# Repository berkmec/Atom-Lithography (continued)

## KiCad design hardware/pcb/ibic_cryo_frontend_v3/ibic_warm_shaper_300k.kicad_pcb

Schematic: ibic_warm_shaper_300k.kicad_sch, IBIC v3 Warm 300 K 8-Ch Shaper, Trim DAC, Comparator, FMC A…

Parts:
CAA0, CAA1, CAA2, CAA3, CAA4, CAA5, CAA6, CAA7: 120pF_C0G_1pct; C_0402_1005Metric; MPN 120pF_C0G_1pct
CD0BN, CD0BP, CD0C, CD0EN, CD0EP, CD1BN, CD1BP, CD1C, CD1EN, CD1EP, CD2BN, CD2BP, CD2C, CD2EN, CD2EP, CD3BN, CD3BP, CD3C, CD3EN, CD3EP, CD4BN, CD4BP, CD4C, CD4EN, CD4EP, CD5BN, CD5BP, CD5C, CD5EN, CD5EP, CD6BN, CD6BP, CD6C, CD6EN, CD6EP, CD7BN, CD7BP, CD7C, CD7EN, CD7EP: 100nF_C0G; C_0402_1005Metric; MPN 100nF_C0G
CDAC0, CDAC1, CDAC2, CDAC3, CDAC4, CDAC5, CDAC6, CDAC7: 100nF_C0G; C_0402_1005Metric; MPN 100nF_C0G
CD_DAC: 100nF_C0G; C_0402_1005Metric; MPN 100nF_C0G
CIN_ULDO_D3V3: 10uF_25V_X7R; C_0805_2012Metric; MPN 10uF_25V_X7R
CIN_ULDO_N2V5, CIN_ULDO_N5A: 10uF_25V_X7R; C_0805_2012Metric; MPN 10uF_25V_X7R
CIN_ULDO_P2V5, CIN_ULDO_P5A: 10uF_25V_X7R; C_0805_2012Metric; MPN 10uF_25V_X7R
COUT_ULDO_D3V3: 10uF_10V_X7R; C_0805_2012Metric; MPN 10uF_10V_X7R
COUT_ULDO_N2V5, COUT_ULDO_N5A: 10uF_10V_X7R; C_0805_2012Metric; MPN 10uF_10V_X7R
COUT_ULDO_P2V5, COUT_ULDO_P5A: 10uF_10V_X7R; C_0805_2012Metric; MPN 10uF_10V_X7R
CP0, CP1, CP2, CP3, CP4, CP5, CP6, CP7: 600pF_C0G_1pct; C_0603_1608Metric; MPN 600pF_C0G_1pct
CREF_DAC: 100nF_C0G; C_0402_1005Metric; MPN 100nF_C0G
CS0, CS1, CS2, CS3, CS4, CS5, CS6, CS7: 600pF_C0G_1pct; C_0603_1608Metric; MPN 600pF_C0G_1pct
CSET_ULDO_D3V3: 4.7uF_10V_X7R; C_0603_1608Metric; MPN 4.7uF_10V_X7R
CSET_ULDO_N2V5, CSET_ULDO_N5A: 4.7uF_10V_X7R; C_0603_1608Metric; MPN 4.7uF_10V_X7R
CSET_ULDO_P2V5, CSET_ULDO_P5A: 4.7uF_10V_X7R; C_0603_1608Metric; MPN 4.7uF_10V_X7R
JADC: FMC_PHA_ADC_TAP_16P; HDR_2x8_2.54mm; MPN FMC_PHA_ADC_TAP_16P
JFPGA: FPGA_COUNT_SPI_24P; HDR_2x12_2.54mm; MPN FPGA_COUNT_SPI_24P
JIN0, JIN1, JIN2, JIN3, JIN4, JIN5, JIN6, JIN7: SMA_50R_FROM_CF63; SMA_EdgeMount; MPN SMA_50R_FROM_CF63
JPWR_COLD_OUT: HDR_6P_CLEAN_REG_OUT; HDR_1x6_2.54mm; MPN HDR_6P_CLEAN_REG_OUT
JPWR_RAW: HDR_6P_LINEAR_PSU_IN; HDR_1x6_2.54mm; MPN HDR_6P_LINEAR_PSU_IN
RAA0, RAA1, RAA2, RAA3, RAA4, RAA5, RAA6, RAA7: 49.9R_1pct; R_0402_1005Metric; MPN 49.9R_1pct
RDAC0, RDAC1, RDAC2, RDAC3, RDAC4, RDAC5, RDAC6, RDAC7: 1.00k_1pct; R_0402_1005Metric; MPN 1.00k_1pct
RG10, RG11, RG12, RG13, RG14, RG15, RG16, RG17: 100R_0.1pct; R_0402_1005Metric; MPN 100R_0.1pct
RG20, RG21, RG22, RG23, RG24, RG25, RG26, RG27: 13.5k_0.1pct; R_0402_1005Metric; MPN 13.5k_0.1pct
RHYS10, RHYS11, RHYS12, RHYS13, RHYS14, RHYS15, RHYS16, RHYS17: 1.00k_1pct; R_0402_1005Metric; MPN 1.00k_1pct
RHYS20, RHYS21, RHYS22, RHYS23, RHYS24, RHYS25, RHYS26, RHYS27: 1.00M_1pct; R_0402_1005Metric; MPN 1.00M_1pct
RRX0, RRX1, RRX2, RRX3, RRX4, RRX5, RRX6, RRX7: 49.9R_1pct; R_0402_1005Metric; MPN 49.9R_1pct
RS10, RS11, RS12, RS13, RS14, RS15, RS16, RS17, RS20, RS21, RS22, RS23, RS24, RS25, RS26, RS27: 2.00k_0.1pct; R_0402_1005Metric; MPN 2.00k_0.1pct
RSET_ULDO_D3V3: 33.2k_0.1pct; R_0402_1005Metric; MPN 33.2k_0.1pct
RSET_ULDO_N2V5: 24.9k_0.1pct; R_0402_1005Metric; MPN 24.9k_0.1pct
RSET_ULDO_N5A: 49.9k_0.1pct; R_0402_1005Metric; MPN 49.9k_0.1pct
RSET_ULDO_P2V5: 24.9k_0.1pct; R_0402_1005Metric; MPN 24.9k_0.1pct
RSET_ULDO_P5A: 49.9k_0.1pct; R_0402_1005Metric; MPN 49.9k_0.1pct
RTERM0, RTERM1, RTERM2, RTERM3, RTERM4, RTERM5, RTERM6, RTERM7: 49.9R_1pct; R_0402_1005Metric; MPN 49.9R_1pct
R_STAR: 0R_STAR_GND; R_0603_1608Metric; MPN 0R_STAR_GND
U0B, U1B, U2B, U3B, U4B, U5B, U6B, U7B: ADA4817-1_SHAPER; SOIC-8-1EP_3.9x4.9mm_P1.27mm; MPN ADA4817-1ARDZ
U0C, U1C, U2C, U3C, U4C, U5C, U6C, U7C: TLV3501_CMP_4p5NS; SOT-23-6; MPN TLV3501AIDBVR
U0E, U1E, U2E, U3E, U4E, U5E, U6E, U7E: ADA4817-1_ADC_BUF; SOIC-8-1EP_3.9x4.9mm_P1.27mm; MPN ADA4817-1ARDZ
UDAC: DAC8568_16B_8CH_SPI; TSSOP-16_4.4x5mm_P0.65mm; MPN DAC8568ICPWR
ULDO_D3V3: LT3045_D3V3_LDO; MSOP-12-1EP_3x4mm_P0.65mm; MPN LT3045EMSE
ULDO_N2V5: LT3094_N2V5_LDO; MSOP-12-1EP_3x4mm_P0.65mm; MPN LT3094EMSE
ULDO_N5A: LT3094_N5V_LDO; MSOP-12-1EP_3x4mm_P0.65mm; MPN LT3094EMSE
ULDO_P2V5: LT3045_P2V5_LDO; MSOP-12-1EP_3x4mm_P0.65mm; MPN LT3045EMSE
ULDO_P5A: LT3045_P5V_LDO; MSOP-12-1EP_3x4mm_P0.65mm; MPN LT3045EMSE

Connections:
AGND: CAA0.2, CAA1.2, CAA2.2, CAA3.2, CAA4.2, CAA5.2, CAA6.2, CAA7.2, CD0BN.2, CD0BP.2, CD0EN.2, CD0EP.2, CD1BN.2, CD1BP.2, CD1EN.2, CD1EP.2, CD2BN.2, CD2BP.2, CD2EN.2, CD2EP.2, CD3BN.2, CD3BP.2, CD3EN.2, CD3EP.2, CD4BN.2, CD4BP.2, CD4EN.2, CD4EP.2, CD5BN.2, CD5BP.2, CD5EN.2, CD5EP.2, CD6BN.2, CD6BP.2, CD6EN.2, CD6EP.2, CD7BN.2, CD7BP.2, CD7EN.2, CD7EP.2, CDAC0.2, CDAC1.2, CDAC2.2, CDAC3.2, CDAC4.2, CDAC5.2, CDAC6.2, CDAC7.2, CIN_ULDO_N2V5.2, CIN_ULDO_N5A.2, CIN_ULDO_P2V5.2, CIN_ULDO_P5A.2, COUT_ULDO_N2V5.2, COUT_ULDO_N5A.2, COUT_ULDO_P2V5.2, COUT_ULDO_P5A.2, CP0.2, CP1.2, CP2.2, CP3.2, CP4.2, CP5.2, CP6.2, CP7.2, CREF_DAC.2, CSET_ULDO_N2V5.2, CSET_ULDO_N5A.2, CSET_ULDO_P2V5.2, CSET_ULDO_P5A.2, JADC.2, JADC.4, JADC.6, JADC.8, JADC.10, JADC.12, JADC.14, JADC.16, JIN0.2 (GND), JIN1.2 (GND), JIN2.2 (GND), JIN3.2 (GND), JIN4.2 (GND), JIN5.2 (GND), JIN6.2 (GND), JIN7.2 (GND), JPWR_COLD_OUT.5 (AGND1), JPWR_COLD_OUT.6 (AGND2), JPWR_RAW.5 (AGND1), JPWR_RAW.6 (AGND2), RG10.2, RG11.2, RG12.2, RG13.2, RG14.2, RG15.2, RG16.2, RG17.2, RRX0.2, RRX1.2, RRX2.2, RRX3.2, RRX4.2, RRX5.2, RRX6.2, RRX7.2, RS10.2, RS11.2, RS12.2, RS13.2, RS14.2, RS15.2, RS16.2, RS17.2, RSET_ULDO_N2V5.2, RSET_ULDO_N5A.2, RSET_ULDO_P2V5.2, RSET_ULDO_P5A.2, R_STAR.1, ULDO_N2V5.6 (ILIM), ULDO_N2V5.9 (GND), ULDO_N5A.6 (ILIM), ULDO_N5A.9 (GND), ULDO_P2V5.6 (ILIM), ULDO_P2V5.8 (GND), ULDO_P2V5.13 (EP_GND), ULDO_P5A.6 (ILIM), ULDO_P5A.8 (GND), ULDO_P5A.13 (EP_GND)
CH0.CMP_INP: RHYS10.2, RHYS20.1, U0C.3 (IN+)
CH0.CMP_OUT: RHYS20.2, RTERM0.1, U0C.5 (OUT)
CH0.COAX_IN: CS0.1, JIN0.1 (SIG), RRX0.1
CH0.COUNT_HIT: JFPGA.1, RTERM0.2
CH0.CR_OUT: CS0.2, RS10.1, U0B.3 (IN+)
CH0.SHP_ADC: CAA0.1, JADC.1, RAA0.2
CH0.SHP_BUF: RAA0.1, RHYS10.1, U0E.1 (FB), U0E.2 (IN-), U0E.6 (OUT)
CH0.SHP_FB: RG10.1, RG20.1, U0B.2 (IN-)
CH0.SHP_GAIN: RG20.2, RS20.1, U0B.1 (FB), U0B.6 (OUT)
CH0.SHP_OUT: CP0.1, RS20.2, U0E.3 (IN+)
CH0.THRESH: CDAC0.1, RDAC0.2, U0C.1 (IN-)
CH0.THRESH_RAW: RDAC0.1, UDAC.4
CH1.CMP_INP: RHYS11.2, RHYS21.1, U1C.3 (IN+)
CH1.CMP_OUT: RHYS21.2, RTERM1.1, U1C.5 (OUT)
CH1.COAX_IN: CS1.1, JIN1.1 (SIG), RRX1.1
CH1.COUNT_HIT: JFPGA.2, RTERM1.2
CH1.CR_OUT: CS1.2, RS11.1, U1B.3 (IN+)
CH1.SHP_ADC: CAA1.1, JADC.3, RAA1.2
CH1.SHP_BUF: RAA1.1, RHYS11.1, U1E.1 (FB), U1E.2 (IN-), U1E.6 (OUT)
CH1.SHP_FB: RG11.1, RG21.1, U1B.2 (IN-)
CH1.SHP_GAIN: RG21.2, RS21.1, U1B.1 (FB), U1B.6 (OUT)
CH1.SHP_OUT: CP1.1, RS21.2, U1E.3 (IN+)
CH1.THRESH: CDAC1.1, RDAC1.2, U1C.1 (IN-)
CH1.THRESH_RAW: RDAC1.1, UDAC.5
CH2.CMP_INP: RHYS12.2, RHYS22.1, U2C.3 (IN+)
CH2.CMP_OUT: RHYS22.2, RTERM2.1, U2C.5 (OUT)
CH2.COAX_IN: CS2.1, JIN2.1 (SIG), RRX2.1
CH2.COUNT_HIT: JFPGA.3, RTERM2.2
CH2.CR_OUT: CS2.2, RS12.1, U2B.3 (IN+)
CH2.SHP_ADC: CAA2.1, JADC.5, RAA2.2
CH2.SHP_BUF: RAA2.1, RHYS12.1, U2E.1 (FB), U2E.2 (IN-), U2E.6 (OUT)
CH2.SHP_FB: RG12.1, RG22.1, U2B.2 (IN-)
CH2.SHP_GAIN: RG22.2, RS22.1, U2B.1 (FB), U2B.6 (OUT)
CH2.SHP_OUT: CP2.1, RS22.2, U2E.3 (IN+)
CH2.THRESH: CDAC2.1, RDAC2.2, U2C.1 (IN-)
CH2.THRESH_RAW: RDAC2.1, UDAC.6
CH3.CMP_INP: RHYS13.2, RHYS23.1, U3C.3 (IN+)
CH3.CMP_OUT: RHYS23.2, RTERM3.1, U3C.5 (OUT)
CH3.COAX_IN: CS3.1, JIN3.1 (SIG), RRX3.1
CH3.COUNT_HIT: JFPGA.4, RTERM3.2
CH3.CR_OUT: CS3.2, RS13.1, U3B.3 (IN+)
CH3.SHP_ADC: CAA3.1, JADC.7, RAA3.2
CH3.SHP_BUF: RAA3.1, RHYS13.1, U3E.1 (FB), U3E.2 (IN-), U3E.6 (OUT)
CH3.SHP_FB: RG13.1, RG23.1, U3B.2 (IN-)
CH3.SHP_GAIN: RG23.2, RS23.1, U3B.1 (FB), U3B.6 (OUT)
CH3.SHP_OUT: CP3.1, RS23.2, U3E.3 (IN+)
CH3.THRESH: CDAC3.1, RDAC3.2, U3C.1 (IN-)
CH3.THRESH_RAW: RDAC3.1, UDAC.7
CH4.CMP_INP: RHYS14.2, RHYS24.1, U4C.3 (IN+)
CH4.CMP_OUT: RHYS24.2, RTERM4.1, U4C.5 (OUT)
CH4.COAX_IN: CS4.1, JIN4.1 (SIG), RRX4.1
CH4.COUNT_HIT: JFPGA.5, RTERM4.2
CH4.CR_OUT: CS4.2, RS14.1, U4B.3 (IN+)
CH4.SHP_ADC: CAA4.1, JADC.9, RAA4.2
CH4.SHP_BUF: RAA4.1, RHYS14.1, U4E.1 (FB), U4E.2 (IN-), U4E.6 (OUT)
CH4.SHP_FB: RG14.1, RG24.1, U4B.2 (IN-)
CH4.SHP_GAIN: RG24.2, RS24.1, U4B.1 (FB), U4B.6 (OUT)
CH4.SHP_OUT: CP4.1, RS24.2, U4E.3 (IN+)
CH4.THRESH: CDAC4.1, RDAC4.2, U4C.1 (IN-)
CH4.THRESH_RAW: RDAC4.1, UDAC.10
CH5.CMP_INP: RHYS15.2, RHYS25.1, U5C.3 (IN+)
CH5.CMP_OUT: RHYS25.2, RTERM5.1, U5C.5 (OUT)
CH5.COAX_IN: CS5.1, JIN5.1 (SIG), RRX5.1
CH5.COUNT_HIT: JFPGA.6, RTERM5.2
CH5.CR_OUT: CS5.2, RS15.1, U5B.3 (IN+)
CH5.SHP_ADC: CAA5.1, JADC.11, RAA5.2
CH5.SHP_BUF: RAA5.1, RHYS15.1, U5E.1 (FB), U5E.2 (IN-), U5E.6 (OUT)
CH5.SHP_FB: RG15.1, RG25.1, U5B.2 (IN-)
CH5.SHP_GAIN: RG25.2, RS25.1, U5B.1 (FB), U5B.6 (OUT)
CH5.SHP_OUT: CP5.1, RS25.2, U5E.3 (IN+)
CH5.THRESH: CDAC5.1, RDAC5.2, U5C.1 (IN-)
CH5.THRESH_RAW: RDAC5.1, UDAC.11
CH6.CMP_INP: RHYS16.2, RHYS26.1, U6C.3 (IN+)
CH6.CMP_OUT: RHYS26.2, RTERM6.1, U6C.5 (OUT)
CH6.COAX_IN: CS6.1, JIN6.1 (SIG), RRX6.1
CH6.COUNT_HIT: JFPGA.7, RTERM6.2
CH6.CR_OUT: CS6.2, RS16.1, U6B.3 (IN+)
CH6.SHP_ADC: CAA6.1, JADC.13, RAA6.2
CH6.SHP_BUF: RAA6.1, RHYS16.1, U6E.1 (FB), U6E.2 (IN-), U6E.6 (OUT)
CH6.SHP_FB: RG16.1, RG26.1, U6B.2 (IN-)
CH6.SHP_GAIN: RG26.2, RS26.1, U6B.1 (FB), U6B.6 (OUT)
CH6.SHP_OUT: CP6.1, RS26.2, U6E.3 (IN+)
CH6.THRESH: CDAC6.1, RDAC6.2, U6C.1 (IN-)
CH6.THRESH_RAW: RDAC6.1, UDAC.12
CH7.CMP_INP: RHYS17.2, RHYS27.1, U7C.3 (IN+)
CH7.CMP_OUT: RHYS27.2, RTERM7.1, U7C.5 (OUT)
CH7.COAX_IN: CS7.1, JIN7.1 (SIG), RRX7.1
CH7.COUNT_HIT: JFPGA.8, RTERM7.2
CH7.CR_OUT: CS7.2, RS17.1, U7B.3 (IN+)
CH7.SHP_ADC: CAA7.1, JADC.15, RAA7.2
CH7.SHP_BUF: RAA7.1, RHYS17.1, U7E.1 (FB), U7E.2 (IN-), U7E.6 (OUT)
CH7.SHP_FB: RG17.1, RG27.1, U7B.2 (IN-)
CH7.SHP_GAIN: RG27.2, RS27.1, U7B.1 (FB), U7B.6 (OUT)
CH7.SHP_OUT: CP7.1, RS27.2, U7E.3 (IN+)
CH7.THRESH: CDAC7.1, RDAC7.2, U7C.1 (IN-)
CH7.THRESH_RAW: RDAC7.1, UDAC.13
DAC_VREF: CREF_DAC.1, UDAC.8 (VREF)
DGND: CD0C.2, CD1C.2, CD2C.2, CD3C.2, CD4C.2, CD5C.2, CD6C.2, CD7C.2, CD_DAC.2, CIN_ULDO_D3V3.2, COUT_ULDO_D3V3.2, CSET_ULDO_D3V3.2, JFPGA.9, JFPGA.10, JFPGA.11, JFPGA.12, JFPGA.13, JFPGA.14, JFPGA.15, JFPGA.16, JFPGA.21, JFPGA.22, JFPGA.23, JFPGA.24, RSET_ULDO_D3V3.2, R_STAR.2, U0C.2 (V-), U0C.6 (SHDN), U1C.2 (V-), U1C.6 (SHDN), U2C.2 (V-), U2C.6 (SHDN), U3C.2 (V-), U3C.6 (SHDN), U4C.2 (V-), U4C.6 (SHDN), U5C.2 (V-), U5C.6 (SHDN), U6C.2 (V-), U6C.6 (SHDN), U7C.2 (V-), U7C.6 (SHDN), UDAC.1 (LDAC_N), UDAC.14 (GND), ULDO_D3V3.6 (ILIM), ULDO_D3V3.8 (GND), ULDO_D3V3.13 (EP_GND)
SPI_CS_N: JFPGA.19, UDAC.2 (SYNC_N)
SPI_MOSI: JFPGA.18, UDAC.15 (DIN)
SPI_SCLK: JFPGA.17, UDAC.16 (SCLK)
ULDO_D3V3_SET: CSET_ULDO_D3V3.1, RSET_ULDO_D3V3.1, ULDO_D3V3.9 (SET)
ULDO_N2V5_SET: CSET_ULDO_N2V5.1, RSET_ULDO_N2V5.1, ULDO_N2V5.10 (SET)
ULDO_N5A_SET: CSET_ULDO_N5A.1, RSET_ULDO_N5A.1, ULDO_N5A.10 (SET)
ULDO_P2V5_SET: CSET_ULDO_P2V5.1, RSET_ULDO_P2V5.1, ULDO_P2V5.9 (SET)
ULDO_P5A_SET: CSET_ULDO_P5A.1, RSET_ULDO_P5A.1, ULDO_P5A.9 (SET)
VCCA: CD0BP.1, CD0EP.1, CD1BP.1, CD1EP.1, CD2BP.1, CD2EP.1, CD3BP.1, CD3EP.1, CD4BP.1, CD4EP.1, CD5BP.1, CD5EP.1, CD6BP.1, CD6EP.1, CD7BP.1, CD7EP.1, COUT_ULDO_P2V5.1, JPWR_COLD_OUT.1 (VCCA), U0B.7 (V+), U0B.8 (PD), U0E.7 (V+), U0E.8 (PD), U1B.7 (V+), U1B.8 (PD), U1E.7 (V+), U1E.8 (PD), U2B.7 (V+), U2B.8 (PD), U2E.7 (V+), U2E.8 (PD), U3B.7 (V+), U3B.8 (PD), U3E.7 (V+), U3E.8 (PD), U4B.7 (V+), U4B.8 (PD), U4E.7 (V+), U4E.8 (PD), U5B.7 (V+), U5B.8 (PD), U5E.7 (V+), U5E.8 (PD), U6B.7 (V+), U6B.8 (PD), U6E.7 (V+), U6E.8 (PD), U7B.7 (V+), U7B.8 (PD), U7E.7 (V+), U7E.8 (PD), ULDO_P2V5.7 (PGFB), ULDO_P2V5.10 (OUTS), ULDO_P2V5.11 (OUT1), ULDO_P2V5.12 (OUT2)
VCCD: CD0C.1, CD1C.1, CD2C.1, CD3C.1, CD4C.1, CD5C.1, CD6C.1, CD7C.1, CD_DAC.1, COUT_ULDO_D3V3.1, JFPGA.20, U0C.4 (V+), U1C.4 (V+), U2C.4 (V+), U3C.4 (V+), U4C.4 (V+), U5C.4 (V+), U6C.4 (V+), U7C.4 (V+), UDAC.3 (AVDD), UDAC.9 (CLR_N), ULDO_D3V3.7 (PGFB), ULDO_D3V3.10 (OUTS), ULDO_D3V3.11 (OUT1), ULDO_D3V3.12 (OUT2)
VIN_N5: CIN_ULDO_N2V5.1, JPWR_RAW.4 (VIN_N5), ULDO_N2V5.1 (IN1), ULDO_N2V5.2 (IN2), ULDO_N2V5.3 (IN3), ULDO_N2V5.4 (EN_UV), ULDO_N2V5.13 (EP_VIN_N)
VIN_N12: CIN_ULDO_N5A.1, JPWR_RAW.2 (VIN_N12), ULDO_N5A.1 (IN1), ULDO_N5A.2 (IN2), ULDO_N5A.3 (IN3), ULDO_N5A.4 (EN_UV), ULDO_N5A.13 (EP_VIN_N)
VIN_P5: CIN_ULDO_D3V3.1, CIN_ULDO_P2V5.1, JPWR_RAW.3 (VIN_P5), ULDO_D3V3.1 (IN1), ULDO_D3V3.2 (IN2), ULDO_D3V3.3 (IN3), ULDO_D3V3.4 (EN_UV), ULDO_P2V5.1 (IN1), ULDO_P2V5.2 (IN2), ULDO_P2V5.3 (IN3), ULDO_P2V5.4 (EN_UV)
VIN_P12: CIN_ULDO_P5A.1, JPWR_RAW.1 (VIN_P12), ULDO_P5A.1 (IN1), ULDO_P5A.2 (IN2), ULDO_P5A.3 (IN3), ULDO_P5A.4 (EN_UV)
VSSA: CD0BN.1, CD0EN.1, CD1BN.1, CD1EN.1, CD2BN.1, CD2EN.1, CD3BN.1, CD3EN.1, CD4BN.1, CD4EN.1, CD5BN.1, CD5EN.1, CD6BN.1, CD6EN.1, CD7BN.1, CD7EN.1, COUT_ULDO_N2V5.1, JPWR_COLD_OUT.2 (VSSA), U0B.4 (V-), U0B.9 (EP), U0E.4 (V-), U0E.9 (EP), U1B.4 (V-), U1B.9 (EP), U1E.4 (V-), U1E.9 (EP), U2B.4 (V-), U2B.9 (EP), U2E.4 (V-), U2E.9 (EP), U3B.4 (V-), U3B.9 (EP), U3E.4 (V-), U3E.9 (EP), U4B.4 (V-), U4B.9 (EP), U4E.4 (V-), U4E.9 (EP), U5B.4 (V-), U5B.9 (EP), U5E.4 (V-), U5E.9 (EP), U6B.4 (V-), U6B.9 (EP), U6E.4 (V-), U6E.9 (EP), U7B.4 (V-), U7B.9 (EP), U7E.4 (V-), U7E.9 (EP), ULDO_N2V5.8 (PGFB), ULDO_N2V5.11 (OUTS), ULDO_N2V5.12 (OUT)
V_N5A: COUT_ULDO_N5A.1, JPWR_COLD_OUT.4 (V_N5A), ULDO_N5A.8 (PGFB), ULDO_N5A.11 (OUTS), ULDO_N5A.12 (OUT)
V_P5A: COUT_ULDO_P5A.1, JPWR_COLD_OUT.3 (V_P5A), ULDO_P5A.7 (PGFB), ULDO_P5A.10 (OUTS), ULDO_P5A.11 (OUT1), ULDO_P5A.12 (OUT2)

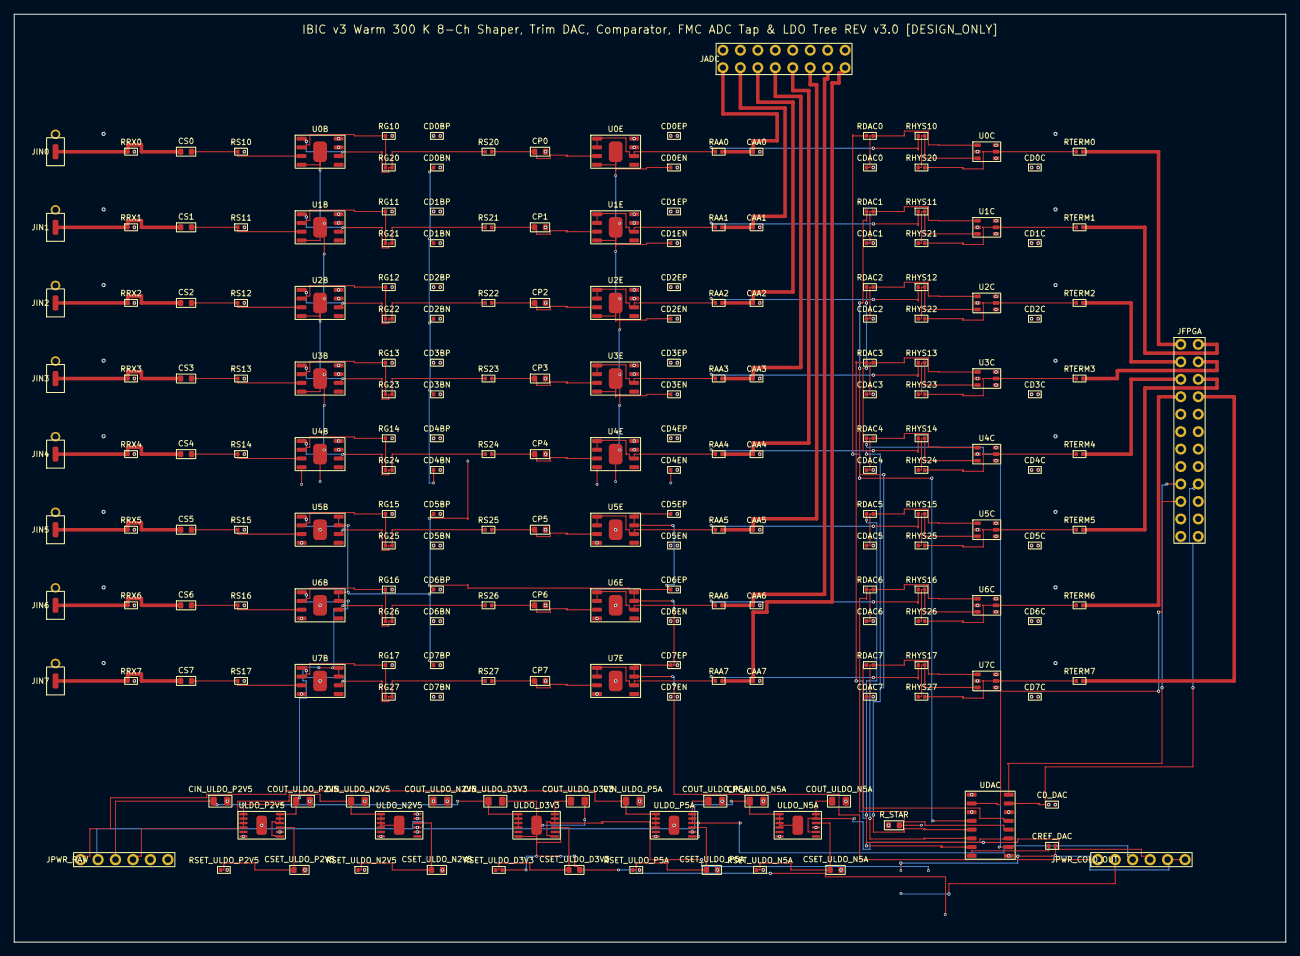
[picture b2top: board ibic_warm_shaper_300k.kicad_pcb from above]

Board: 4 copper layers, 185.0 x 135.0 mm, 217 parts (0 on the bottom side), 116 nets.

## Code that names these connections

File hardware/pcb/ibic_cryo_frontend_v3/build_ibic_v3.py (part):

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    conn("AGND", "JGUARD_IN", 2)
    conn("GUARD_IN", "RGRD_IN", 1)
    conn("GUARD_REF", "RGRD_IN", 2)
    conn("GUARD_REF", "U_GRD_BOOT", 7)     # LTC6268IS8 Pin 7 = +IN
    conn("GUARD_BOOT_OUT", "U_GRD_BOOT", 3) # LTC6268IS8 Pin 3 = OUT
    conn("GUARD_BOOT_OUT", "U_GRD_BOOT", 6) # LTC6268IS8 Pin 6 = -IN (unity-gain follower)
    conn("GUARD_BOOT_OUT", "RGRD_ISO", 1)
    conn("GUARD_DRV", "RGRD_ISO", 2)
    conn("VCCA", "U_GRD_BOOT", 1); conn("VCCA", "U_GRD_BOOT", 2); conn("VSSA", "U_GRD_BOOT", 4)
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        conn(f"HV_BIAS_{p}", diode.ref, 2)
        conn("GUARD_DRV", diode.ref, 3)

        # Ultra-low-C summing node CH{ch}.CSA_SUM (exact LTC6268IS8 S8 pinout: 6=-IN, 7=+IN, 5/8=GUARD_DRV)
        conn(f"{p}.CSA_SUM", diode.ref, 1)
        conn(f"{p}.CSA_SUM", cf.ref, 2)
        conn(f"{p}.CSA_SUM", rf.ref, 2)
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    conn("SPI_SCLK", jfpga.ref, 17); conn("SPI_MOSI", jfpga.ref, 18)
    conn("SPI_CS_N", jfpga.ref, 19); conn("VCCD", jfpga.ref, 20)
    for gpin in (9, 10, 11, 12, 13, 14, 15, 16, 21, 22, 23, 24):
        conn("DGND", jfpga.ref, gpin)

    # JADC AGND return pins (even pins 2,4,...,16)
    for gpin in (2, 4, 6, 8, 10, 12, 14, 16):
        conn("AGND", jadc.ref, gpin)

    dac_out_pins = (4, 5, 6, 7, 10, 11, 12, 13)

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            f"RHYS2{ch}", "1.00M_1pct", "Resistor_SMD:R_0402_1005Metric",
            132.0, yc + 2.3, pins=auto_footprint_pads("0402", ("1", "2")), bom_id="S3.2-02", epistemic_tag="{Pasif-COTS}",
        ))
        # Exact TI SBOS321 DBV SOT-23-6 pinout: 1:-IN, 2:V-, 3:+IN, 4:V+, 5:OUT, 6:SHDN(active-HIGH -> DGND)
        uc = add_c(ComponentSpec(
            f"U{ch}C", "TLV3501_CMP_4p5NS", "Package_TO_SOT_SMD:SOT-23-6",
            141.5, yc,
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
